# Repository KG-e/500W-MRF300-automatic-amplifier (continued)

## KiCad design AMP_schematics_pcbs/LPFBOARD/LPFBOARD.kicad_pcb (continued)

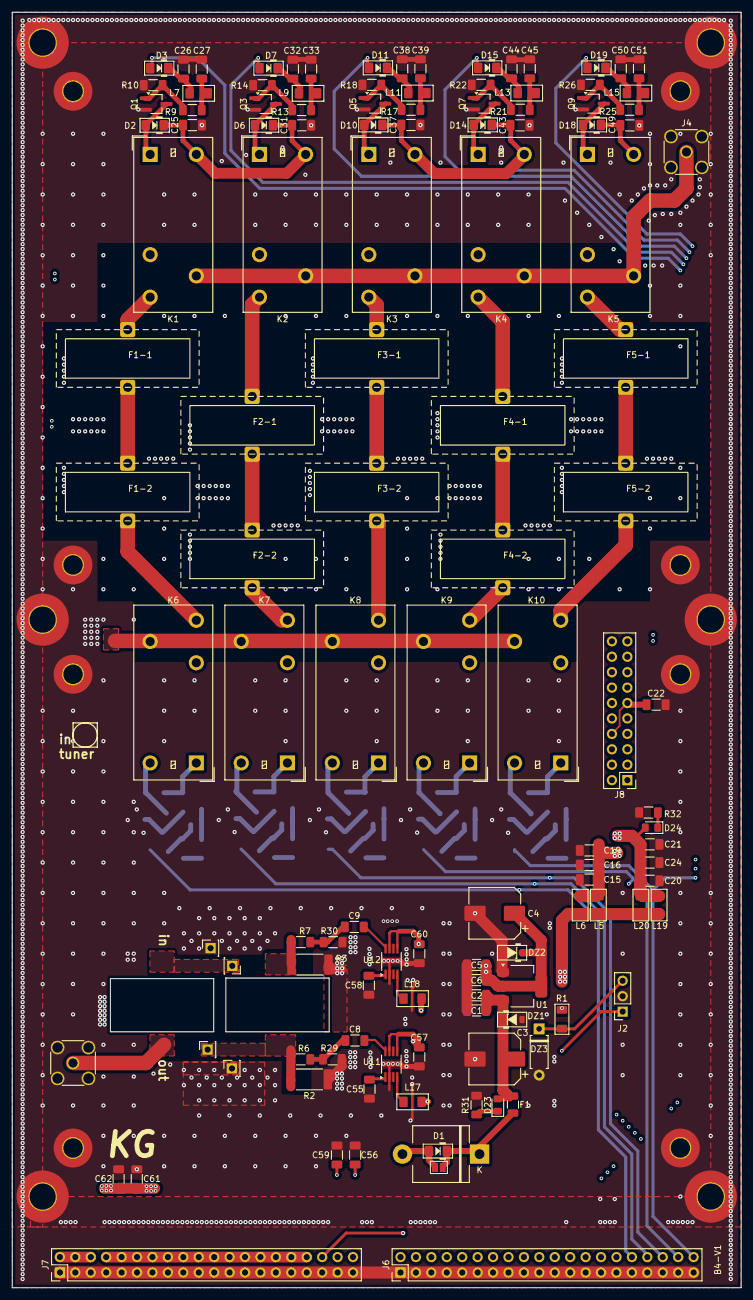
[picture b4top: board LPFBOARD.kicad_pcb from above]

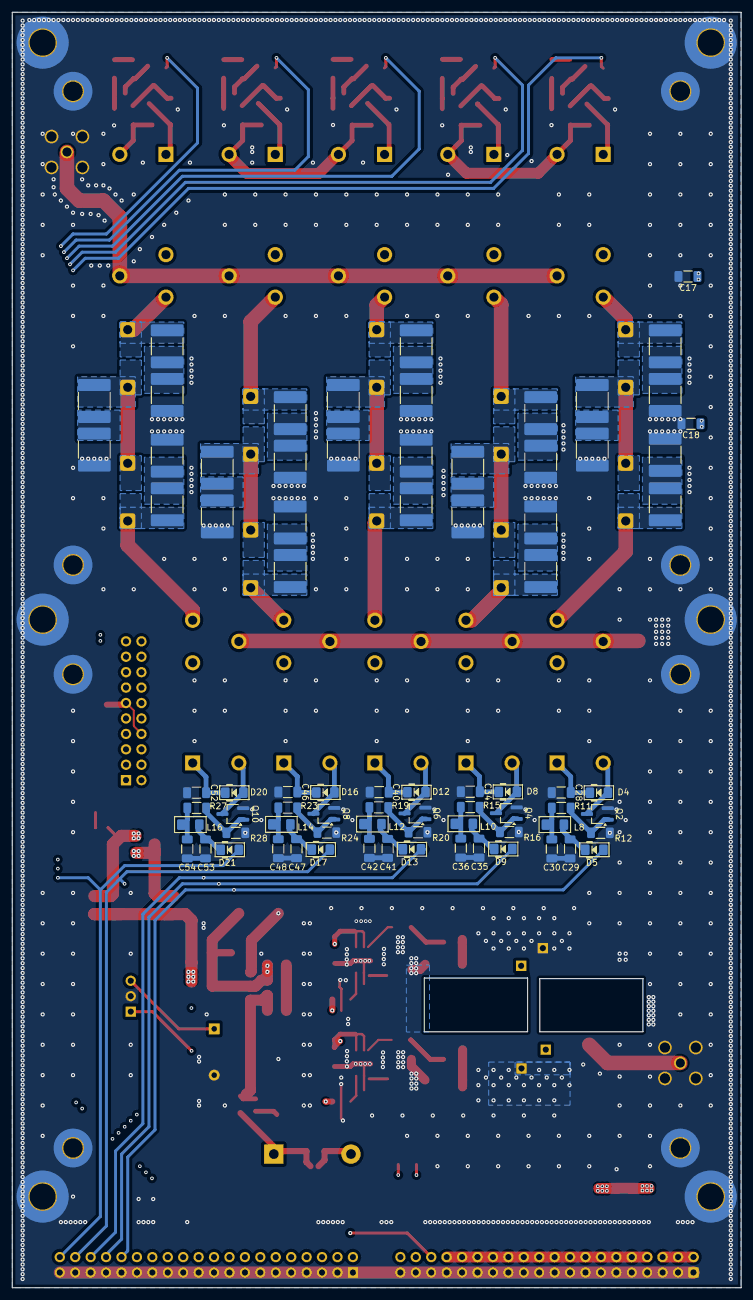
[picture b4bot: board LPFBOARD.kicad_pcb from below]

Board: 4 copper layers, 120.0 x 210.0 mm, 216 parts (77 on the bottom side), 116 nets.

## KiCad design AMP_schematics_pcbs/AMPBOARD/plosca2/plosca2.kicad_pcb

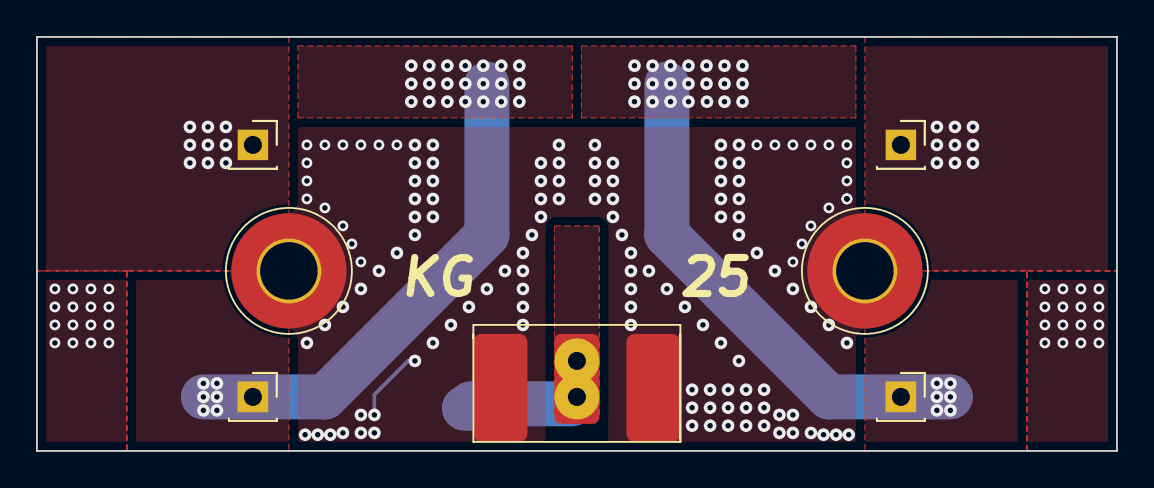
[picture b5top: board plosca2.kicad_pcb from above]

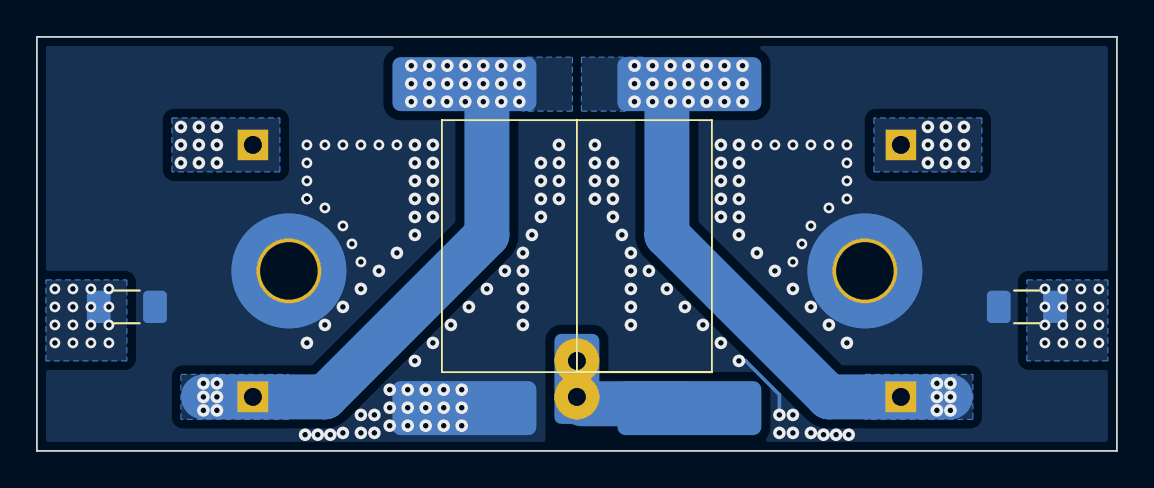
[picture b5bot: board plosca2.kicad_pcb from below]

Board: 2 copper layers, 60.0 x 23.0 mm, 10 parts (3 on the bottom side), 4 nets.

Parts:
C5, C7: C; C_1206_3216Metric_Pad1.33x1.80mm_HandSolder
H1, H2: MountingHole_Pad; MountingHole_3.2mm_M3_Pad_TopBottom
J1: Conn_Coaxial; SMA-smd
J2, J3, J4, J5: Conn_01x01_Pin; PinSocket_1x01_P2.54mm_Vertical
T1: Transformer_1P_1S; trans-mali

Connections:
/in: J1.1 (In), T1.1 (AA)
/t1: J2.1, T1.4 (SB)
/t2: J3.1, T1.3 (SA)
GNDPWR: C5.1, C7.2, H1.1, H2.1, J1.2 (Ext), T1.2 (AB)

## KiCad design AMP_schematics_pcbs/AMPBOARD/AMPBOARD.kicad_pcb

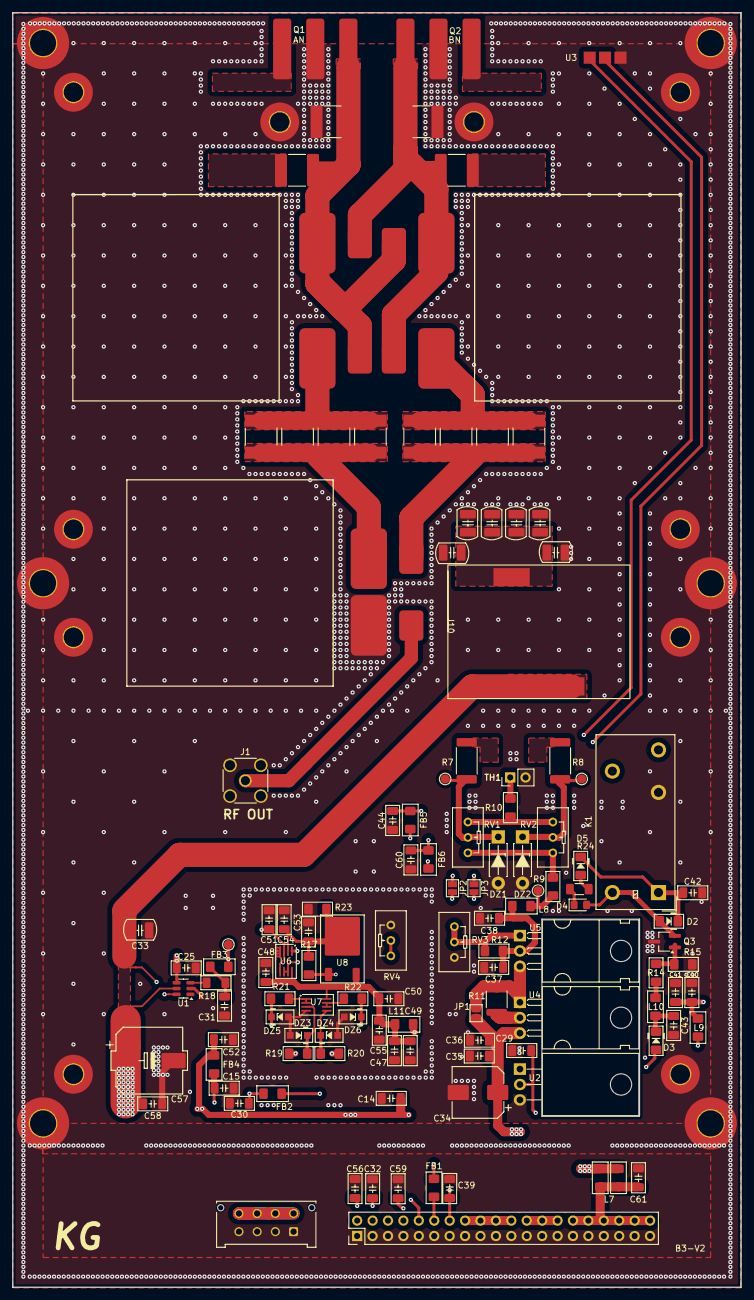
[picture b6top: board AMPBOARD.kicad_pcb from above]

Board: 4 copper layers, 120.0 x 210.0 mm, 140 parts (0 on the bottom side), 55 nets.

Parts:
C1, C2, C3, C6, C7, C9, C10, C11, C45, C46: C; C_2220_5750Metric_Pad1.97x5.40mm_HandSolder
C5, C13: 100p; C_2220_5750Metric_Pad1.97x5.40mm_HandSolder
C14, C15, C25, C29, C30, C32, C36, C38, C41, C42, C43, C44, C48, C49, C50, C52, C53, C56, C58, C59, C60, C61: 100n; C_1206_3216Metric_Pad1.33x1.80mm_HandSolder
C16: 22n; C_1210_3225Metric_Pad1.42x2.65mm
C17, C20, C23, C24, C28: C; C_1210_3225Metric_Pad1.42x2.65mm
C31, C35, C37, C54, C55: 1u; C_1206_3216Metric_Pad1.33x1.80mm_HandSolder
C33: 10u; C_1210_3225Metric_Pad1.42x2.65mm
C34: 56u/63V; CP_Elec_8x10
C39, C40, C47: 10n; C_1206_3216Metric_Pad1.33x1.80mm_HandSolder
C51: C; C_1206_3216Metric_Pad1.33x1.80mm_HandSolder
C57: 300u/63V; CP_Elec_10x10
D2, D3, D5: D; D_1206_3216Metric_Pad1.42x1.75mm_HandSolder
D4: LED; LED_0805_2012Metric_Pad1.15x1.40mm_HandSolder
DZ1, DZ2: 5V; D_DO-41_SOD81_P7.62mm_Horizontal_Zener
DZ3, DZ4, DZ5, DZ6: 5V; D_SOD-123F_Zener
FB1, FB2, FB3, FB4, FB5, FB6: FerriteBead; Ferrite_1206_3216Metric_Pad1.42x1.75mm_BigPads
H1, H2, H3, H4, H5, H13: MountingHole_Pad; MountingHole_4.3mm_M4_Pad_TopBottom
H6, H7, H8, H9, H10, H11, H12, H14, H15, H16: MountingHole_Pad; MountingHole_3.2mm_M3_Pad_TopBottom
J1: Conn_Coaxial; SMA_Amphenol_132134_Vertical
J3: Conn_02x20_Counter_Clockwise; PinHeader_2x20_P2.54mm_Vertical
J4: Conn_02x04_Counter_Clockwise; Molex_Micro-Fit_3.0_43045-0812_2x04_P3.00mm_Vertical
J5, J6, J7, J8, J9, J10: Conn_01x02_Pin; TransCoax-povezava
J11: Conn_01x02_Pin; PinHeader_1x02_P2.54mm_Vertical
JP1, JP2, JP3: SolderJumper_2_Open; SolderJumper-2_P1.3mm_Open_Pad1.0x1.5mm
K1: Relay_SPDT-jw1; Relay_SPDT_Panasonic_JW1_FormC
L6: 15turns on 43; choke-amp
L7, L8, L12: L_Ferrite_Small; Ferrite_1206_3216Metric_Pad1.42x1.75mm_BigPads
L9, L11: L_Ferrite; Ferrite_1206_3216Metric_Pad1.42x1.75mm_BigPads
L10: L; Ferrite_1206_3216Metric_Pad1.42x1.75mm_BigPads
Q1: NMOS; MRF300AN
Q2: NMOS; MRF300BN
Q3: Q_NMOS-D_Generic_GDS; TSOT-23_HandSoldering
R7, R8: 100R; R_2512_6332Metric_Pad1.40x3.35mm_HandSolder
R9, R10, R17: 2kR; R_1206_3216Metric_Pad1.42x1.75mm_HandSolder
R11: R; R_1812_4532Metric
R12: 500R; R_1206_3216Metric_Pad1.42x1.75mm_HandSolder
R14: 300R; R_1206_3216Metric_Pad1.42x1.75mm_HandSolder
R15: 5kR; R_1206_3216Metric_Pad1.42x1.75mm_HandSolder
R18: 330R; R_1206_3216Metric_Pad1.30x1.75mm_HandSolder
R19, R20, R21, R22, R23: 1kR; R_1206_3216Metric_Pad1.42x1.75mm_HandSolder
R24: 2k; R_1206_3216Metric_Pad1.30x1.75mm_HandSolder
RV1, RV2: 1kR; Potentiometer_Bourns_3296W_Vertical
RV3: 10k; Potentiometer_Bourns_3296W_Vertical
RV4: 10kR; Potentiometer_Bourns_3296W_Vertical
TP1: BIAS; TestPoint_Pad_D1.5mm
TP2: B2; TestPoint_Pad_D1.5mm
TP3: B1; TestPoint_Pad_D1.5mm
TP5: I; TestPoint_Pad_D1.5mm
U1: MAX40010; SOT-23-6
U2: LM35-LP; TO-220-3_Horizontal_TabDown
U3: LM35-LP; TO-220-3 smd
U4, U5: LM317AT; TO-220-3_Horizontal_TabDown
U6, U7: Opamp_Dual; SSOP-8_2.95x2.8mm_P0.65mm
U8: LM317MKVU; TO-252-2

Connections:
5V-3: C14.1, C25.1, C52.1, FB4.2, J3.16, J3.18, J3.20, J3.22, U1.4 (VDD), U2.1 (+V_{S})
12V-3: J3.24, J3.26, J3.28, L9.2, L11.2
12V-OP: C47.1, C48.1, C49.1, C50.1, C55.2, L11.1, U6.8 (V+), U7.8 (V+), U8.3 (IN)
50V-1: C33.2, C57.1, C58.1, J4.5, J4.6, J4.7, J4.8, L6.2, U1.5 (RS+), U1.6 (RS-)
50V-2: C61.1, J3.30, J3.32, J3.34, J3.36, J3.38, J3.40, L7.1, L12.1
/dov: C16.2, C17.2, C20.2, C23.2, C24.2, C28.2, L6.1
B1: DZ1.1 (K), JP2.1 (A), R7.1, RV1.2, TP3.1
B1buff: C56.1, DZ5.1 (K), J3.2, R21.2
B2: DZ2.1 (K), JP3.1 (A), R8.1, RV2.2, TP2.1
B2buff: C59.1, DZ6.1 (K), J3.8, R22.2
BIAS: L8.2, R9.2, TP1.1
BIAS-OFF: K1.6, R9.1, RV1.1, RV2.1
BIAS-ON: C39.1, D3.2 (A), J3.14
D1: C5.2, C45.2, J5.1, J7.2, J8.1, Q1.1 (D)
D2: C13.2, C46.2, J5.2, J6.1, J7.1, Q2.1 (D)
GNDD: C5.1, C13.1, C14.2, C15.2, C16.1, C17.1, C20.1, C23.1, C24.1, C25.2, C28.1, C29.2, C30.2, C31.2, C32.2, C33.1, C34.2, C35.2, C36.2, C37.2, C38.2, C39.2, C40.2, C41.2, C42.2, C43.2, C44.2, C47.2, C48.2, C49.2, C50.2, C51.1, C52.2, C53.1, C54.1, C55.1, C56.2, C57.2, C58.2, C59.2, C60.2, C61.2, DZ1.2 (A), DZ2.2 (A), DZ3.2 (A), DZ4.2 (A), DZ5.2 (A), DZ6.2 (A), H1.1, H2.1, H3.1, H4.1, H5.1, H6.1, H7.1, H8.1, H9.1, H10.1, H11.1, H12.1, H13.1, H14.1, H15.1, H16.1, J1.2 (Ext), J3.1, J3.3, J3.5, J3.7, J3.9, J3.11, J3.13, J3.15, J3.17, J3.19, J3.21, J3.23, J3.25, J3.27, J3.29, J3.31, J3.33, J3.35, J3.37, J3.39, J4.1, J4.2, J4.3, J4.4, J10.2, J11.2, K1.2, Q1.3 (S), Q2.3 (S), Q3.3 (S), R15.2, R23.1, RV3.1, RV4.1, U1.2 (GND), U2.3 (GND), U3.3 (GND), U6.4 (V-), U7.4 (V-)
I-sense: C51.2, FB3.2, TP5.1, U6.3 (+), U6.5 (+)
Ibuff: C32.1, J3.4, U6.6 (-), U6.7
unnamed: C15.1, FB4.1, FB5.2
unnamed: C30.1, FB2.1, FB6.2
unnamed: C31.1, FB3.1, R18.2
unnamed: D2.2 (A), D4.2 (A), K1.8, Q3.2 (D)
unnamed: C43.1, D3.1 (K), L10.1
unnamed: D4.1 (K), R24.1
unnamed: D5.2 (A), R24.2
unnamed: DZ3.1 (K), R19.2, U7.3 (+)
unnamed: DZ4.1 (K), R20.2, U7.5 (+)
unnamed: J11.1, R10.2
unnamed: C34.1, C35.1, C36.1, JP1.1 (A), L7.2, L12.2, U4.3 (IN)
unnamed: JP1.2 (B), R11.2, U4.1, U5.3 (IN)
unnamed: JP2.2 (B), R19.1
unnamed: JP3.2 (B), R20.1
unnamed: L10.2, R14.1
unnamed: Q3.1 (G), R14.2, R15.1
unnamed: R10.1, RV1.3, RV2.3
unnamed: R12.1, RV3.2, RV3.3, U5.1
unnamed: R17.1, RV4.2, RV4.3, U8.1
unnamed: R18.1, U1.3 (OUT)
unnamed: C29.1, FB1.1, U2.2 (V_{OUT})
unnamed: C44.1, FB5.1, U3.1 (+V_{S})
unnamed: C60.1, FB6.1, U3.2 (V_{OUT})
unnamed: R11.1, U4.2 (OUT)
unnamed: C37.1, C38.1, L8.1, R12.2, U5.2 (OUT)
unnamed: C53.2, C54.2, R17.2, R23.2, U6.2 (-), U8.2 (OUT)
unnamed: R21.1, U7.1, U7.2 (-)
unnamed: R22.1, U7.6 (-), U7.7
PWRRL3: C40.1, C41.1, C42.1, D2.1 (K), D5.1 (K), K1.1, L9.1
T1: FB1.2, J3.12
T2: FB2.2, J3.10
izh: J1.1 (In), J10.1
izh1: C1.1, C2.1, C3.1, C6.1, J6.2
izh1po: C1.2, C2.2, C3.2, C6.2, J9.1
izh2: C7.1, C9.1, C10.1, C11.1, J8.2
izh2po: C7.2, C9.2, C10.2, C11.2, J9.2
overcurrent: J3.6, U6.1

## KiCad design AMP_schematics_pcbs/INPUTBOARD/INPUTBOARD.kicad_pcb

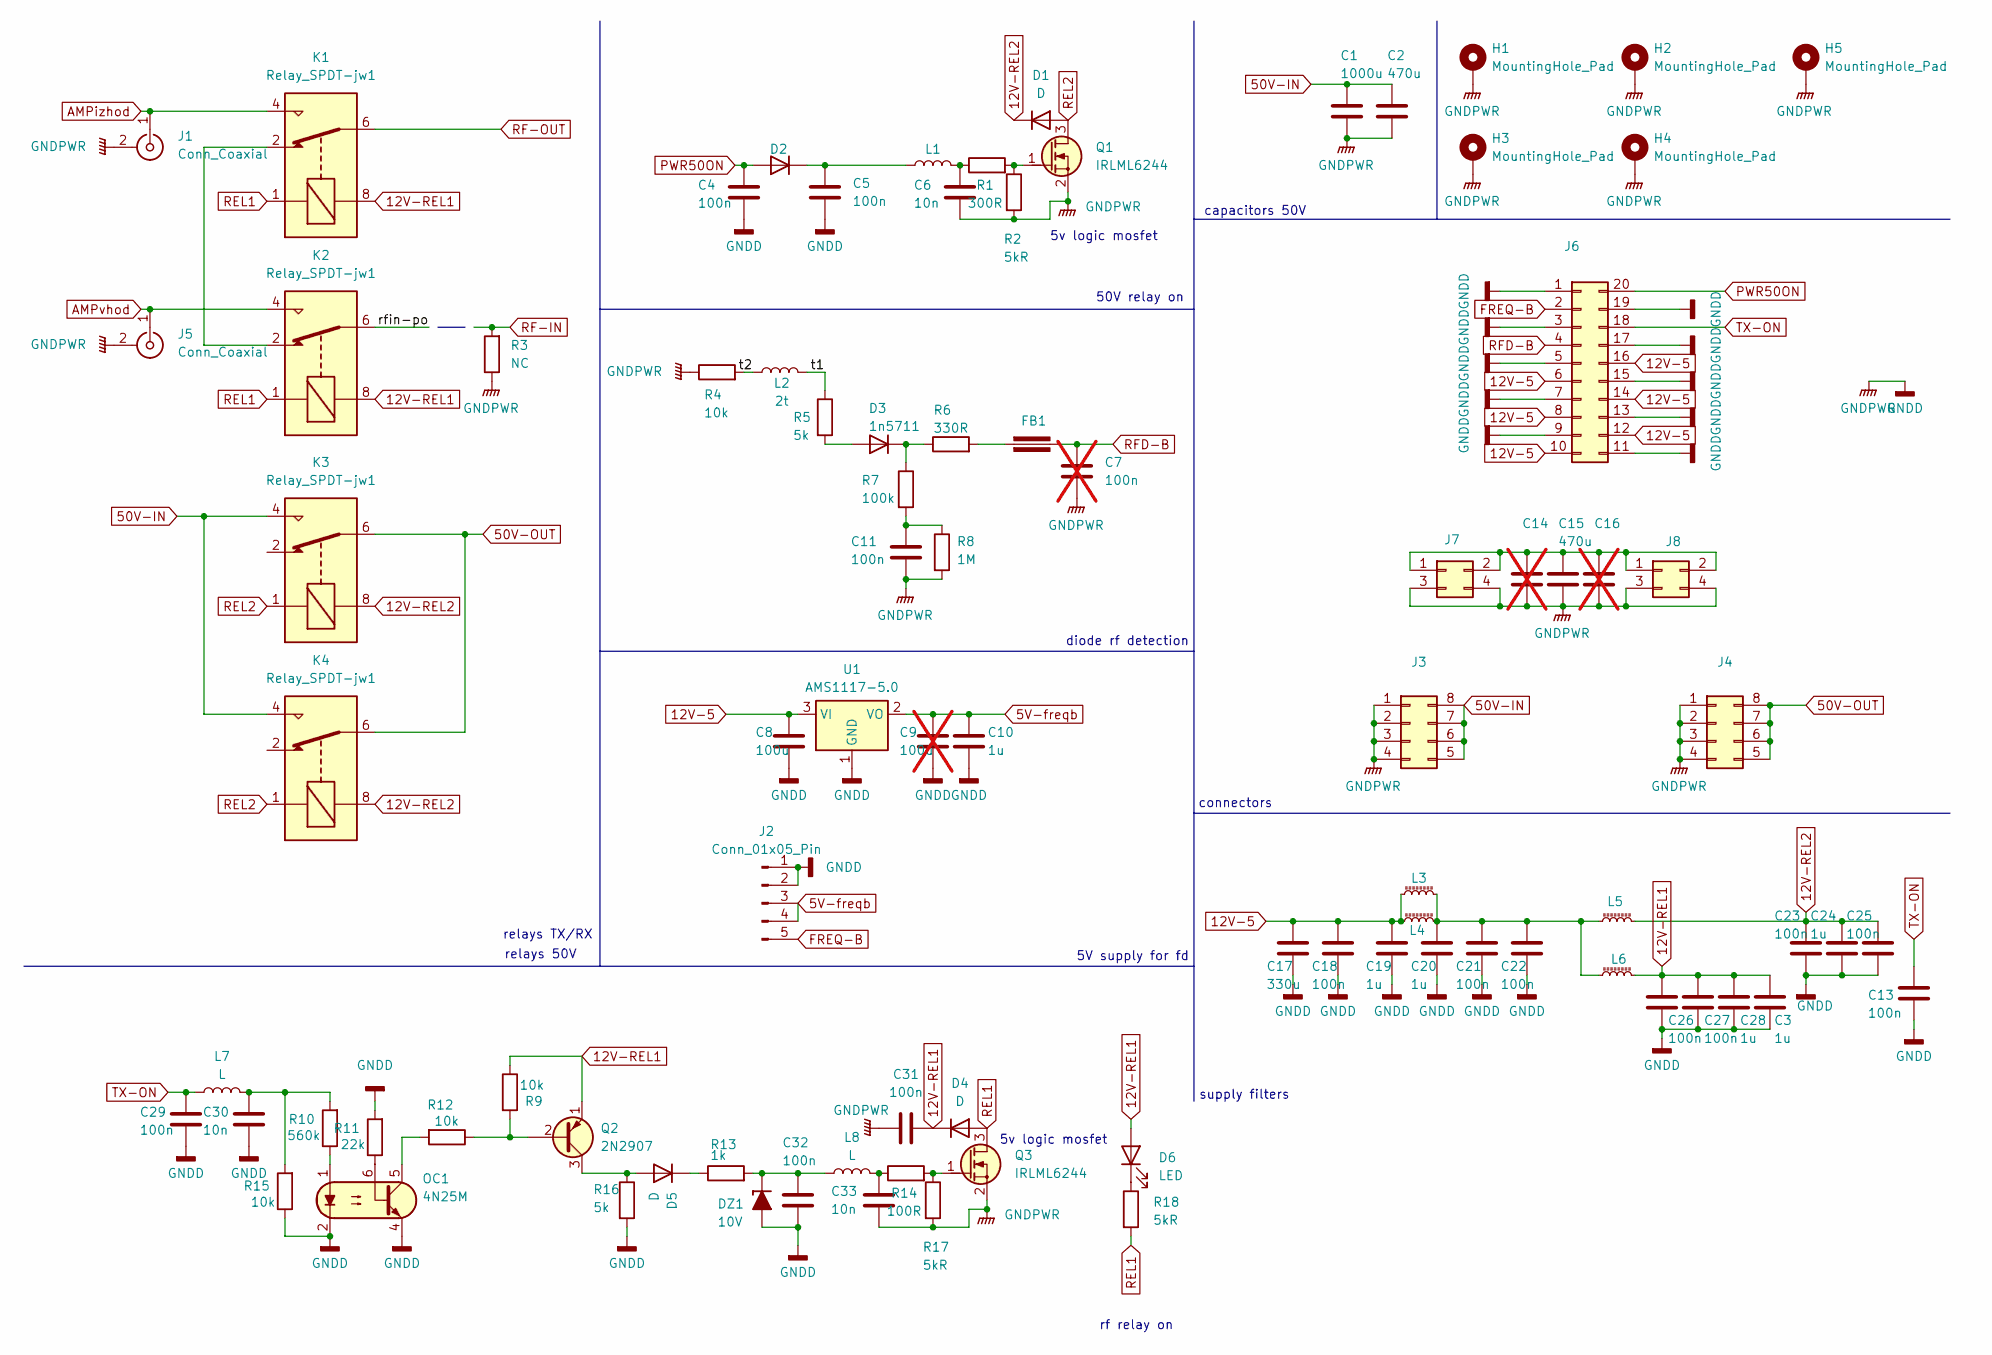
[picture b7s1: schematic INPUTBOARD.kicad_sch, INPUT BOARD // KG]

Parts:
C1: 1000u; CP_Radial_D12.5mm_P5.00mm
C2: 470u; CP_Radial_D16.0mm_P7.50mm
C3, C10, C19, C20, C24, C28: 1u; C_1206_3216Metric_Pad1.33x1.80mm_HandSolder
C4, C5, C11, C13, C18, C21, C22, C23, C25, C26, C27, C29, C31, C32: 100n; C_1206_3216Metric_Pad1.33x1.80mm_HandSolder
C6, C30, C33: 10n; C_1206_3216Metric_Pad1.33x1.80mm_HandSolder
C7: 100n; C_1206_3216Metric_Pad1.33x1.80mm_HandSolder; not fitted
C8: 100u; CP_EIA-7343-30_AVX-N_HandSolder
C9: 100u; CP_EIA-7343-30_AVX-N_HandSolder; not fitted
C14, C16: C; CP_Radial_D10.0mm_P5.00mm; not fitted
C15: 470u; CP_Radial_D10.0mm_P5.00mm
C17: 330u; CP_Elec_8x10
D1, D2, D4, D5: D; D_1206_3216Metric_Pad1.42x1.75mm_HandSolder
D3: 1n5711; D_DO-35_SOD27_P7.62mm_Horizontal
D6: LED; LED_0805_2012Metric_Pad1.15x1.40mm_HandSolder
DZ1: 10V; D_DO-35_SOD27_P7.62mm_Horizontal
FB1: Ferrite_Bead; Ferrite_1206_3216Metric_Pad1.22x1.90mm_BigPads
H1, H2, H3, H4, H5: MountingHole_Pad; MountingHole_3.5mm_Pad
J1, J5: Conn_Coaxial; SMA_Amphenol_132134_Vertical
J2: Conn_01x05_Pin; plosca-frek
J3, J4: Conn_02x04_Counter_Clockwise; Molex_Micro-Fit_3.0_43045-0812_2x04_P3.00mm_Vertical
J6: Conn_02x10_Counter_Clockwise; PinHeader_1x20_P1.27mm_Vertical
J7, J8: Conn_02x02_Odd_Even; Molex_Micro-Fit_3.0_43045-0412_2x02_P3.00mm_Vertical
K1, K2: Relay_SPDT-jw1; relej-izhodni
K3, K4: Relay_SPDT-jw1; relej-prozoren16A
L1, L7, L8: L; Ferrite_1206_3216Metric_Pad1.42x1.75mm_BigPads
L2: 2t; Ferrite_1206_3216Metric_Pad1.42x1.75mm_BigPads
L3, L4, L5, L6: L_Ferrite_Small; Ferrite_1206_3216Metric_Pad1.22x1.90mm_BigPads
OC1: 4N25M; DIP-6_W7.62mm_LongPads
Q1, Q3: IRLML6244; SOT-23_Handsoldering
Q2: 2N2907; TO-18-3_EBC
R1: 300R; R_1206_3216Metric_Pad1.30x1.75mm_HandSolder
R2, R17, R18: 5kR; R_1206_3216Metric_Pad1.30x1.75mm_HandSolder
R3: NC; R_1206_3216Metric
R4, R9, R12, R15: 10k; R_1206_3216Metric_Pad1.30x1.75mm_HandSolder
R5, R16: 5k; R_1206_3216Metric_Pad1.30x1.75mm_HandSolder
R6: 330R; R_1206_3216Metric_Pad1.30x1.75mm_HandSolder
R7: 100k; R_1206_3216Metric_Pad1.30x1.75mm_HandSolder
R8: 1M; R_1206_3216Metric_Pad1.30x1.75mm_HandSolder
R10: 560k; R_1206_3216Metric_Pad1.30x1.75mm_HandSolder
R11: 22k; R_1206_3216Metric_Pad1.30x1.75mm_HandSolder
R13: 1k; R_1206_3216Metric_Pad1.30x1.75mm_HandSolder
R14: 100R; R_1206_3216Metric_Pad1.30x1.75mm_HandSolder
U1: AMS1117-5.0; SOT-223-3_TabPin2

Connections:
5V-freqb: C9.1, C10.1, J2.3, J2.4, U1.2 (VO)
12V-5: C8.1, C17.1, C18.1, C19.1, J6.6, J6.8, J6.10, J6.12, J6.14, J6.16, L3.1, L4.1, U1.3 (VI)
12V-REL1: C3.1, C26.1, C27.1, C28.1, C31.1, D4.1 (K), D6.2 (A), K1.8, K2.8, L6.2, Q2.1 (E), R9.1
12V-REL2: C23.1, C24.1, C25.1, D1.1 (K), K3.8, K4.8, L5.2
50V-IN: C1.1, C2.1, J3.5, J3.6, J3.7, J3.8, K3.4, K4.4
50V-OUT: J4.5, J4.6, J4.7, J4.8, K3.6, K4.6
/rfin-po: K2.6
/t1: L2.2, R5.1
/t2: L2.1, R4.2
AMPizhod: J1.1 (In), K1.4
AMPvhod: J5.1 (In), K2.4
FREQ-B: J2.5, J6.2
GNDD: C1.2, C2.2, C3.2, C4.2, C5.2, C6.2, C7.2, C8.2, C9.2, C10.2, C11.2, C13.2, C14.2, C15.2, C16.2, C17.2, C18.2, C19.2, C20.2, C21.2, C22.2, C23.2, C24.2, C25.2, C26.2, C27.2, C28.2, C29.2, C30.2, C31.2, C32.2, C33.2, DZ1.2 (A), H1.1, H2.1, H3.1, H4.1, H5.1, J1.2 (Ext), J2.1, J2.2, J3.1, J3.2, J3.3, J3.4, J4.1, J4.2, J4.3, J4.4, J5.2 (Ext), J6.1, J6.3, J6.5, J6.7, J6.9, J6.11, J6.13, J6.15, J6.17, J6.19, J7.3, J7.4, J8.3, J8.4, OC1.2, OC1.4, Q1.2 (S), Q3.2 (S), R2.2, R3.1, R4.1, R8.2, R11.2, R15.1, R16.2, R17.2, U1.1 (GND)
unnamed: C6.1, L1.2, R1.1
unnamed: C11.1, R7.2, R8.1
unnamed: C20.1, C21.1, C22.1, L3.2, L4.2, L5.1, L6.1
unnamed: C30.1, L7.2, R10.2, R15.2
unnamed: C33.1, L8.2, R14.1
unnamed: C5.1, D2.1 (K), L1.1
unnamed: D3.2 (A), R5.2
unnamed: D3.1 (K), R6.1, R7.1
unnamed: D5.2 (A), Q2.3 (C), R16.1
unnamed: D5.1 (K), R13.1
unnamed: D6.1 (K), R18.1
unnamed: C32.1, DZ1.1 (K), L8.1, R13.2
unnamed: FB1.1, R6.2
unnamed: C14.1, C15.1, C16.1, J7.1, J7.2, J8.1, J8.2
unnamed: K1.2, K2.2
unnamed: OC1.1, R10.1
unnamed: OC1.5, R12.2
unnamed: OC1.6, R11.1
unnamed: Q1.1 (G), R1.2, R2.1
unnamed: Q2.2 (B), R9.2, R12.1
unnamed: Q3.1 (G), R14.2, R17.1
PWR50ON: C4.1, D2.2 (A), J6.20
REL1: D4.2 (A), K1.1, K2.1, Q3.3 (D), R18.2
REL2: D1.2 (A), K3.1, K4.1, Q1.3 (D)
RF-IN: R3.2
RF-OUT: K1.6
RFD-B: C7.1, FB1.2, J6.4
TX-ON: C13.1, C29.1, J6.18, L7.1

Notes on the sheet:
relays TX/RX
diode rf detection
5v logic mosfet
capacitors 50V
5V supply for fd
rf relay on
relays 50V
supply filters
connectors
50V relay on

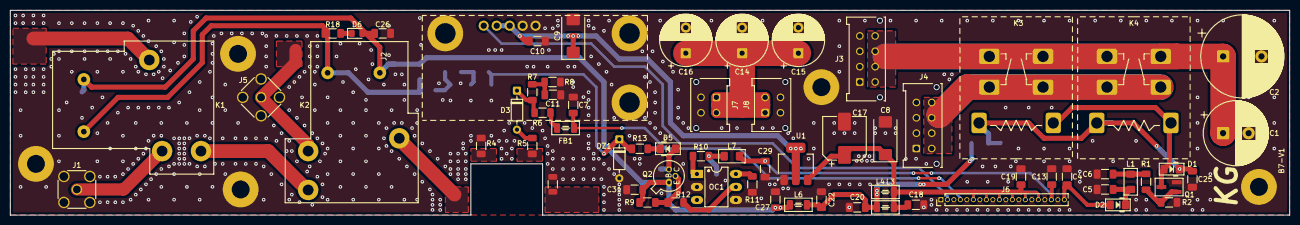
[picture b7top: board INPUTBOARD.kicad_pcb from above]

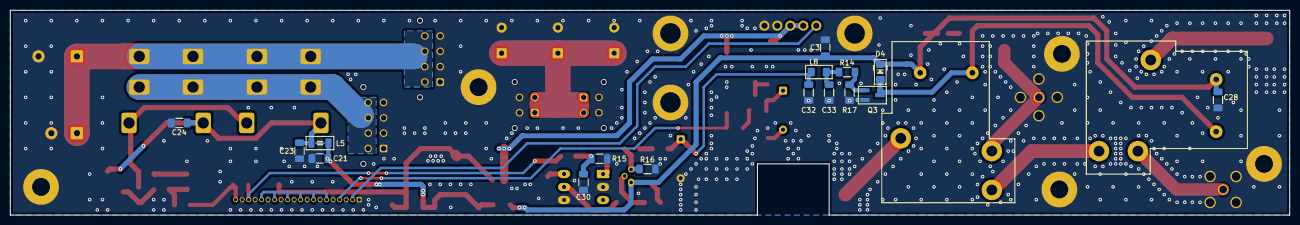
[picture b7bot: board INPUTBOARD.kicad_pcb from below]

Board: 2 copper layers, 250.0 x 40.0 mm, 87 parts (18 on the bottom side), 36 nets.

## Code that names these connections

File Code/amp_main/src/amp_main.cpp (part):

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  FAULT_UART_COMM           = 7,   // UART comm/heartbeat/sync latched
  FAULT_ADC_HARDWARE        = 8,   // ADS1115 / I²C bus fault (rate-limited)
  FAULT_CURRENT_SENSOR      = 9,   // Iamp reads near-zero with meaningful Pout — sensor failed
  FAULT_BIAS_STARTUP        = 10,  // bias current didn't rise within timeout
  FAULT_TUNE_UNSTABLE       = 20,  // freq. unstable during tune (ssb)
  FAULT_INPUT_TOO_HIGH_HW   = 21,  // input too high (over 120W)
  FAULT_ATT_VERIFY          = 22,  // power was too high after att. switch
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  FAULT_TEMP_HIGH           = 50,  // heatsink ≥70°C / inner ≥55°C / air ≥50°C — soft fault
  FAULT_TEMP_CRITICAL       = 51,  // heatsink ≥80°C — hard fault (MOSFET case temp)
  FAULT_LOW_VOLTAGE         = 60,  // 18V or 50V rail out of range
  FAULT_HIGH_CURRENT_AVR    = 61,  // overcurrent caught by AVR ADC (SR latch backup)
  FAULT_GATE_DRIFT          = 62,  // checkProtectionSlow tripped — thermal runaway suspect
  FAULT_PA_SUPPLY_LOW       = 63,  // 50V requested, not achieved
  FAULT_PA_SUPPLY_STUCK     = 64,  // 50V not requested, still present
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// ================= PIN DEFINITIONS =================

// Attenuator board OUTPUT (D30–D37 = PORTC on ATmega2560)
#define att1  30
#define att2  31
#define att3  32
#define att4  33
#define att5  34
#define att6  35
#define att7  36
#define att8  37
#define rfout A7

// Amplifier board OUTPUT
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#define LPF5 A12

// Tuner board OUTPUT
#define TBL1   A13   // CTR1 on schematic
#define TBL2   A14
#define TBL3   A15
#define TBL4   29    // inductor bypass
#define TBL5   28
#define TBL6   27
#define TBL7   26    // CTR7 on schematic

#define TBC1   25    // CTR8 on schematic
#define TBC2   24
#define TBC3   23
#define TBC4   22    // capacitor adding
#define TBC5   10
#define TBC6   11
#define TBC7   12    // CTR14 on schematic

#define TBLCsw 13    // CTR15 — capacitance location

// Misc
#define highvsupplyon A5  // OUTPUT — 50V supply on
#define rfswitch      38  // OUTPUT — switch relays RX→TX
#define buzzer        49  // OUTPUT — alarm buzzer
#define QofSR         16  // INPUT  — SR latch output (50V overcurrent hardware trip)
#define RofSR         17  // OUTPUT — SR latch reset (only after fault acknowledged)
#define rfdetection   A4  // INPUT  — diode RF detector
#define rffrequency    2  // INPUT  — frequency detector (INT4, 0–2kHz pin freq * 16384 = actual RF Hz)
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// ================= PIN INIT =================

void AMP_pin_init() {
  pinMode(att1, OUTPUT);  digitalWrite(att1, LOW);
  pinMode(att2, OUTPUT);  digitalWrite(att2, LOW);
  pinMode(att3, OUTPUT);  digitalWrite(att3, LOW);
  pinMode(att4, OUTPUT);  digitalWrite(att4, LOW);
  pinMode(att5, OUTPUT);  digitalWrite(att5, LOW);
  pinMode(att6, OUTPUT);  digitalWrite(att6, LOW);
  pinMode(att7, OUTPUT);  digitalWrite(att7, LOW);
  pinMode(att8, OUTPUT);  digitalWrite(att8, LOW);

  pinMode(rfout, OUTPUT); digitalWrite(rfout, LOW);

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
#define MAX_INPUT_POWER_EMERGENCY 17.0f

#define ATT_PORT PORTC  // att1–att8 = D30–D37 = PORTC on ATmega2560
                        // 0x00 = all stages engaged (min power) — safe state
                        // 0xFF = all stages bypassed (max power) — never use as default

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  ADC_init();

  // Timer1 — free-running counter used as a time reference for the INT4-based
  // frequency detector. NOT input capture (ICP1 would be PB0/pin 48); the ISR
  // samples TCNT1 manually. /8 prescaler → 0.5us per tick.
  TCCR1A = 0;
  TCCR1B = (1 << CS11);   // prescaler /8, normal mode (no WGM bits set)

  // INT4 rising edge (PE4 = pin 2 on ATmega2560)
  EICRB |= (1 << ISC41) | (1 << ISC40);
  EIMSK |= (1 << INT4);

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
